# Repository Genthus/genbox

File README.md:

# GenBox
A leverless fightstick with ergonomic button placement as well as plenty of space for custom art!

# Sources

This project made use of the following:
- [Kicad](https://www.kicad.org/)
- [FreeCad Link](https://github.com/realthunder/FreeCAD)
- [Keebio-Parts.pretty](https://github.com/keebio/Keebio-Parts.pretty?tab=MIT-1-ov-file)
- [KiCad-SSD1306_OLED-0.91-128x32](https://github.com/MichMich/KiCad-SSD1306_OLED-0.91-128x32)
- [Tri-Hard-slab-v2](https://github.com/Rev1s10n/Tri-Hard-slab-v2?tab=readme-ov-file)

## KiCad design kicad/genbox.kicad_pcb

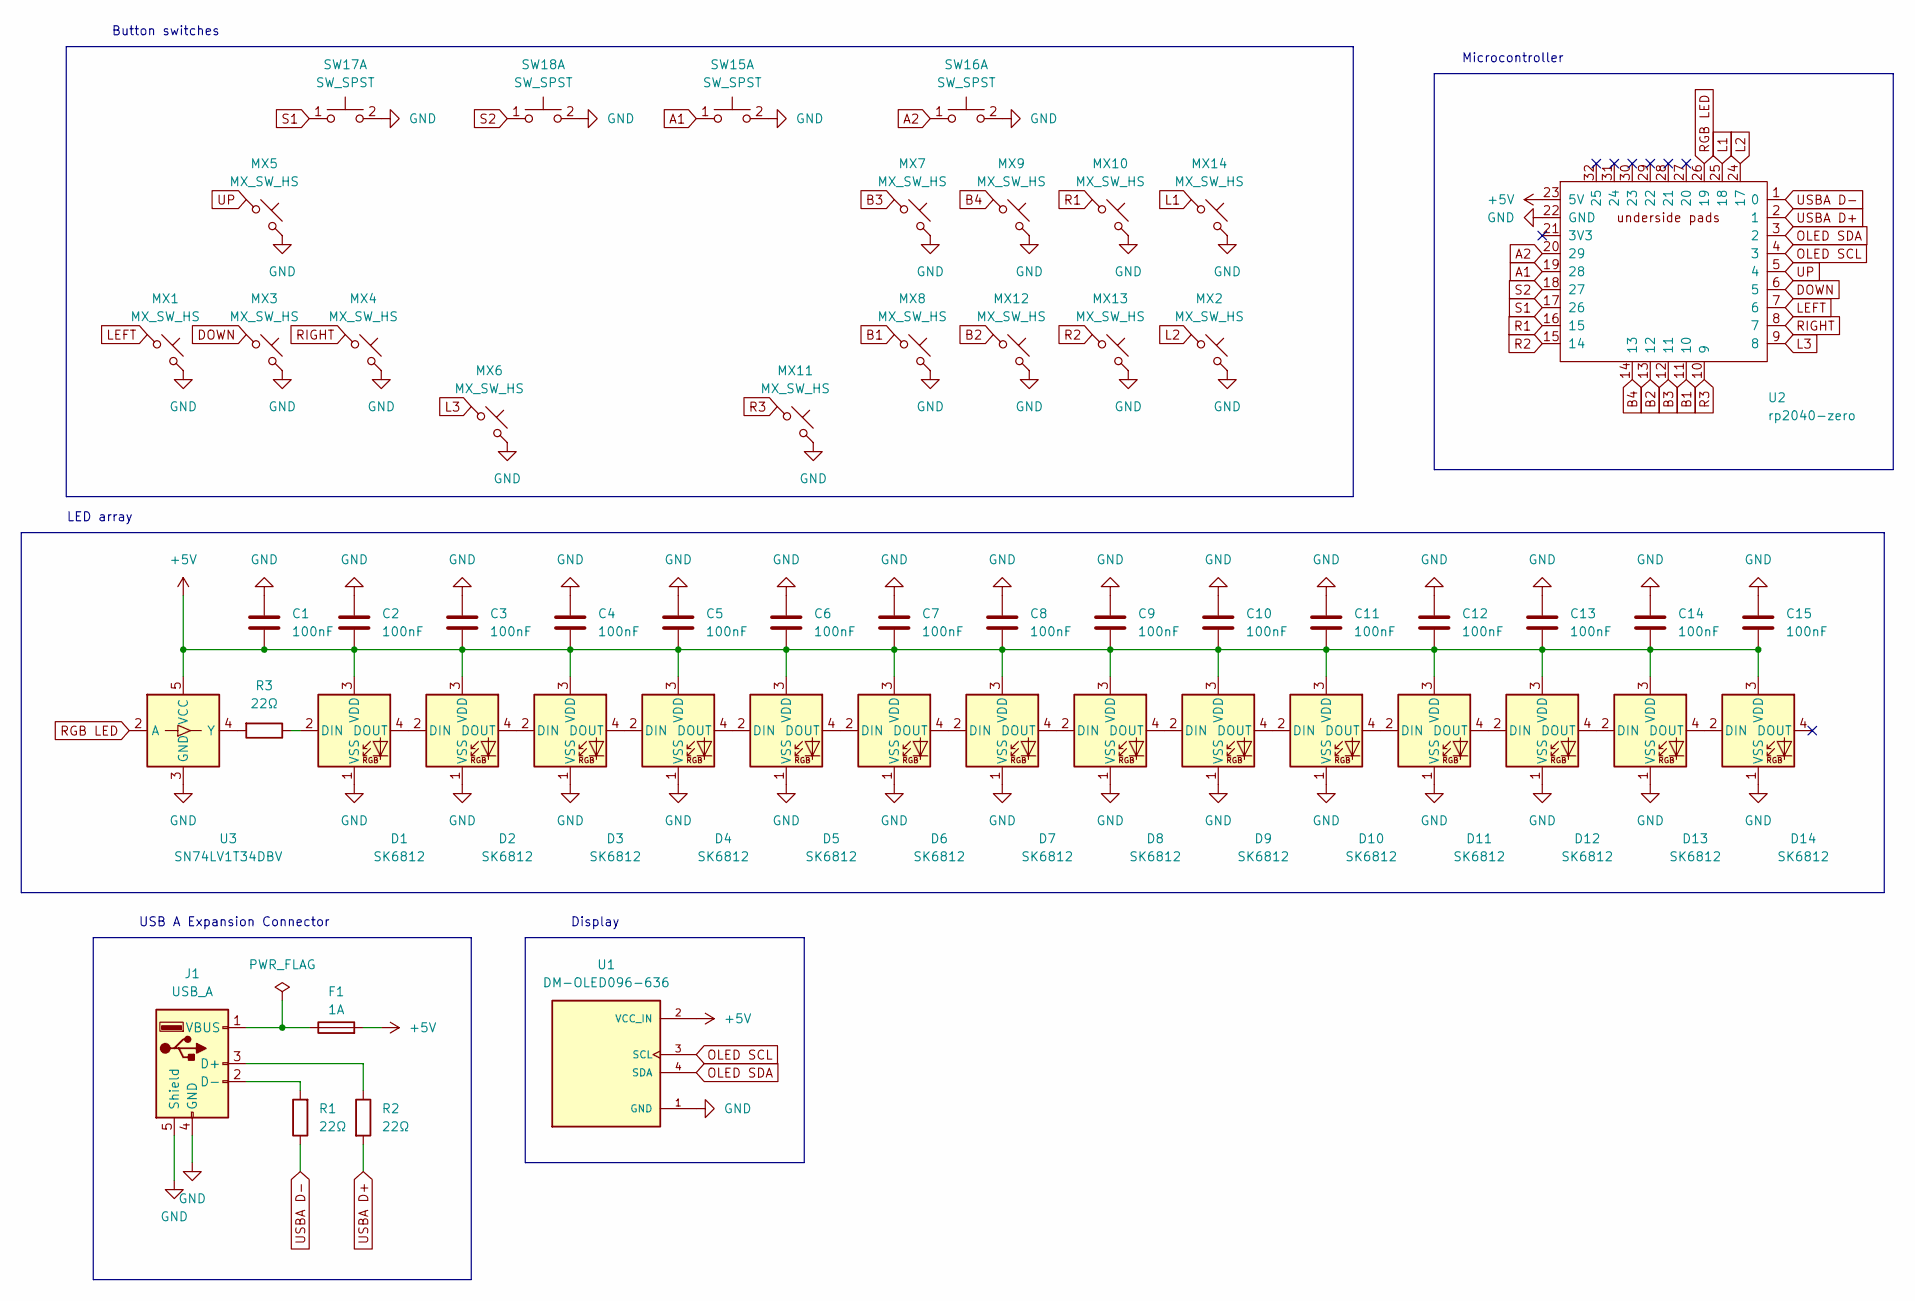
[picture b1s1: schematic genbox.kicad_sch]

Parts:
C1, C2, C3, C4, C5, C6, C7, C8, C9, C10, C11, C12, C13, C14, C15: 100nF; C_0805_2012Metric_Pad1.18x1.45mm_HandSolder; LCSC Part # C2169363
D1, D2, D3, D4, D5, D6, D7, D8, D9, D10, D11, D12, D13, D14: SK6812; SK6812-MINI-E_MX; LCSC Part # C5149201
F1: 1A; Fuse_0805_2012Metric_Pad1.15x1.40mm_HandSolder; LCSC Part # C116170
J1: USB_A; USB_A_Receptacle_GCT_USB1046; LCSC Part # C2689981
MX1, MX2, MX3, MX4, MX5, MX6, MX7, MX8, MX9, MX10, MX11, MX12, MX13, MX14: MX_SW_HS; SW_MX_HS_1u; LCSC Part # C5184526
R1, R2, R3: 22Ω; R_0603_1608Metric_Pad0.98x0.95mm_HandSolder; LCSC Part # C23345
SW15, SW16, SW17, SW18: SW_SPST; SW_PUSH-12mm_centered; LCSC Part # C455212
U1: DM-OLED096-636; MODULE_DM-OLED096-636; PARTREV 2018-09-10; LCSC Part # C5248080
U2: rp2040-zero; rp2040-zero-smd-pads; LCSC Part # C5350143
U3: SN74LV1T34DBV; SOT-23-5; LCSC Part # C100024

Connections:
+5V: C1.2, C2.2, C3.2, C4.2, C5.2, C6.2, C7.2, C8.2, C9.2, C10.2, C11.2, C12.2, C13.2, C14.2, C15.2, D1.3 (VDD), D2.3 (VDD), D3.3 (VDD), D4.3 (VDD), D5.3 (VDD), D6.3 (VDD), D7.3 (VDD), D8.3 (VDD), D9.3 (VDD), D10.3 (VDD), D11.3 (VDD), D12.3 (VDD), D13.3 (VDD), D14.3 (VDD), F1.2, U1.2 (VCC_IN), U2.23 (5V), U3.5 (VCC)
A1: SW15.1 (C), U2.19 (28)
A2: SW16.1 (C), U2.20 (29)
B1: MX8.1, U2.11 (10)
B2: MX12.1, U2.13 (12)
B3: MX7.1, U2.12 (11)
B4: MX9.1, U2.14 (13)
DOWN: MX3.1, U2.6 (5)
GND: C1.1, C2.1, C3.1, C4.1, C5.1, C6.1, C7.1, C8.1, C9.1, C10.1, C11.1, C12.1, C13.1, C14.1, C15.1, D1.1 (VSS), D2.1 (VSS), D3.1 (VSS), D4.1 (VSS), D5.1 (VSS), D6.1 (VSS), D7.1 (VSS), D8.1 (VSS), D9.1 (VSS), D10.1 (VSS), D11.1 (VSS), D12.1 (VSS), D13.1 (VSS), D14.1 (VSS), J1.4 (GND), J1.5 (Shield), MX1.2, MX2.2, MX3.2, MX4.2, MX5.2, MX6.2, MX7.2, MX8.2, MX9.2, MX10.2, MX11.2, MX12.2, MX13.2, MX14.2, SW15.2 (D), SW16.2 (D), SW17.2 (D), SW18.2 (D), U1.1 (GND), U2.22 (GND), U2.33 (GND), U3.3 (GND)
L1: MX14.1, U2.25 (18)
L2: MX2.1, U2.24 (17)
L3: MX6.1, U2.9 (8)
LEFT: MX1.1, U2.7 (6)
unnamed: D1.2 (DIN), R3.1
unnamed: D1.4 (DOUT), D2.2 (DIN)
unnamed: D2.4 (DOUT), D3.2 (DIN)
unnamed: D3.4 (DOUT), D4.2 (DIN)
unnamed: D4.4 (DOUT), D5.2 (DIN)
unnamed: D5.4 (DOUT), D6.2 (DIN)
unnamed: D6.4 (DOUT), D7.2 (DIN)
unnamed: D7.4 (DOUT), D8.2 (DIN)
unnamed: D8.4 (DOUT), D9.2 (DIN)
unnamed: D9.4 (DOUT), D10.2 (DIN)
unnamed: D10.4 (DOUT), D11.2 (DIN)
unnamed: D11.4 (DOUT), D12.2 (DIN)
unnamed: D12.4 (DOUT), D13.2 (DIN)
unnamed: D13.4 (DOUT), D14.2 (DIN)
unnamed: J1.3 (D+), R2.1
unnamed: J1.2 (D-), R1.2
unnamed: F1.1, J1.1 (VBUS)
unnamed: R3.2, U3.4 (Y)
OLED SCL: U1.3 (SCL), U2.4 (3)
OLED SDA: U1.4 (SDA), U2.3 (2)
R1: MX10.1, U2.16 (15)
R2: MX13.1, U2.15 (14)
R3: MX11.1, U2.10 (9)
RGB LED: U2.26 (19), U3.2 (A)
RIGHT: MX4.1, U2.8 (7)
S1: SW17.1 (C), U2.17 (26)
S2: SW18.1 (C), U2.18 (27)
UP: MX5.1, U2.5 (4)
USBA D+: R2.2, U2.2 (1)
USBA D-: R1.1, U2.1 (0)

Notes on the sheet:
Microcontroller
Display
LED array
USB A Expansion Connector
Button switches

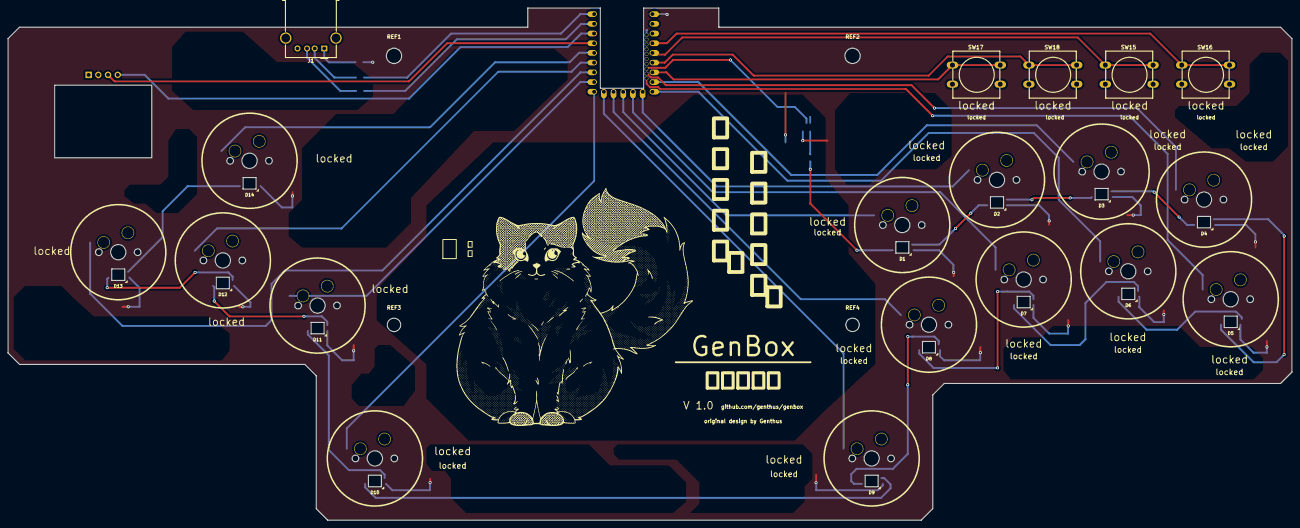
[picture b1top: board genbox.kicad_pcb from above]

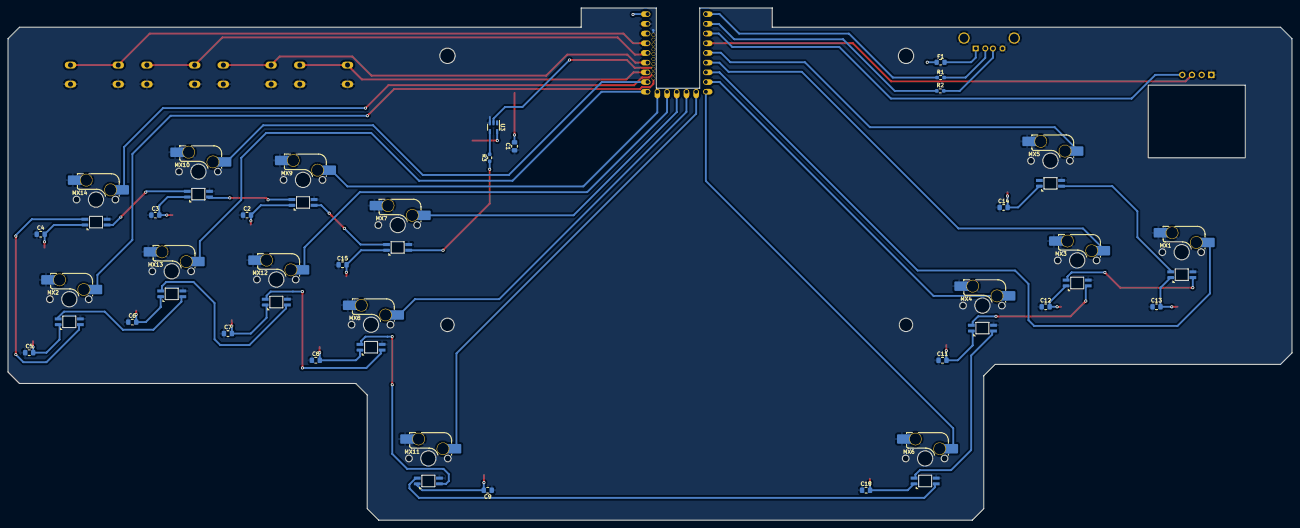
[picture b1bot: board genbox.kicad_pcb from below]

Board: 2 copper layers, 336.0 x 134.0 mm, 59 parts (35 on the bottom side), 43 nets.

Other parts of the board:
REF1, REF2: MountingHole_4mm
REF3, REF4: MountingHole_3.5mm

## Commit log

2024-02-03 removed release and compiled files
2024-02-03 removed gerber zip
2024-02-04 fixed gitignore
2024-02-04 doubled trace width
2024-02-04 changed freecad filename
2024-02-04 pcb dimension changes
2024-02-04 readme update
2024-02-04 fix readme image
2024-02-04 i cannot count
2024-02-04 moved drill holes
2024-02-06 rework p1
2024-02-06 converted to freecad link branch
2024-02-07 pcb rework complete
2024-02-07 pcb handsolder adjustments
2024-02-07 reworked 5+v traces
2024-02-07 added mounting holes
2024-02-07 mounting hole sketch
2024-02-07 usb a connection switch
2024-02-07 fixed usb position
2024-02-07 thickened case, fixed bottom chamfer
2024-02-07 moved case files
2024-02-07 added simple case
2024-02-07 pcb adjustments and readme
2024-02-08 fixed bad geometry
2024-02-09 added button
2024-02-09 improved button design
2024-02-09 added inside fillet to button
2024-02-09 remove backup files & update gitignore
2024-02-09 added case readme, changed screw size, removed svg files
2024-02-10 model updates
2024-02-10 added case version 2
2024-02-10 added readme
2024-02-10 changed picture
2024-02-10 changed folder names
2024-02-10 more name changes
2024-02-17 updated names and reworked 2 piece case
2024-02-21 increased OLED hole, enlarged rp2040 pads
2024-02-21 fixed kicad footprint path
